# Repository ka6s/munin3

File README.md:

# munin3
This is a KICAD version of the Munin 3 100W amplifer designed by Kjell - LA2NI. Note that some of the DNI parts have been left out of the schematic. 

The design has been updated to the point that it reliably can balance the two transistors. Haven't verified the
Test Point for that operation yet.

Kjell, LA2NI has reviewed the design and found an error on my part when I did flooding of the power 
transformer.  Kicad didn't really do what I expected. I had to beef up these connections by hand. He also
found a couple errors in my schematic, and I found another later.. these issues have all been 
fixed.

The amplifier seems to work! 

Use the files in gerbers/munin3_v1.1.zip

Steve KA6S

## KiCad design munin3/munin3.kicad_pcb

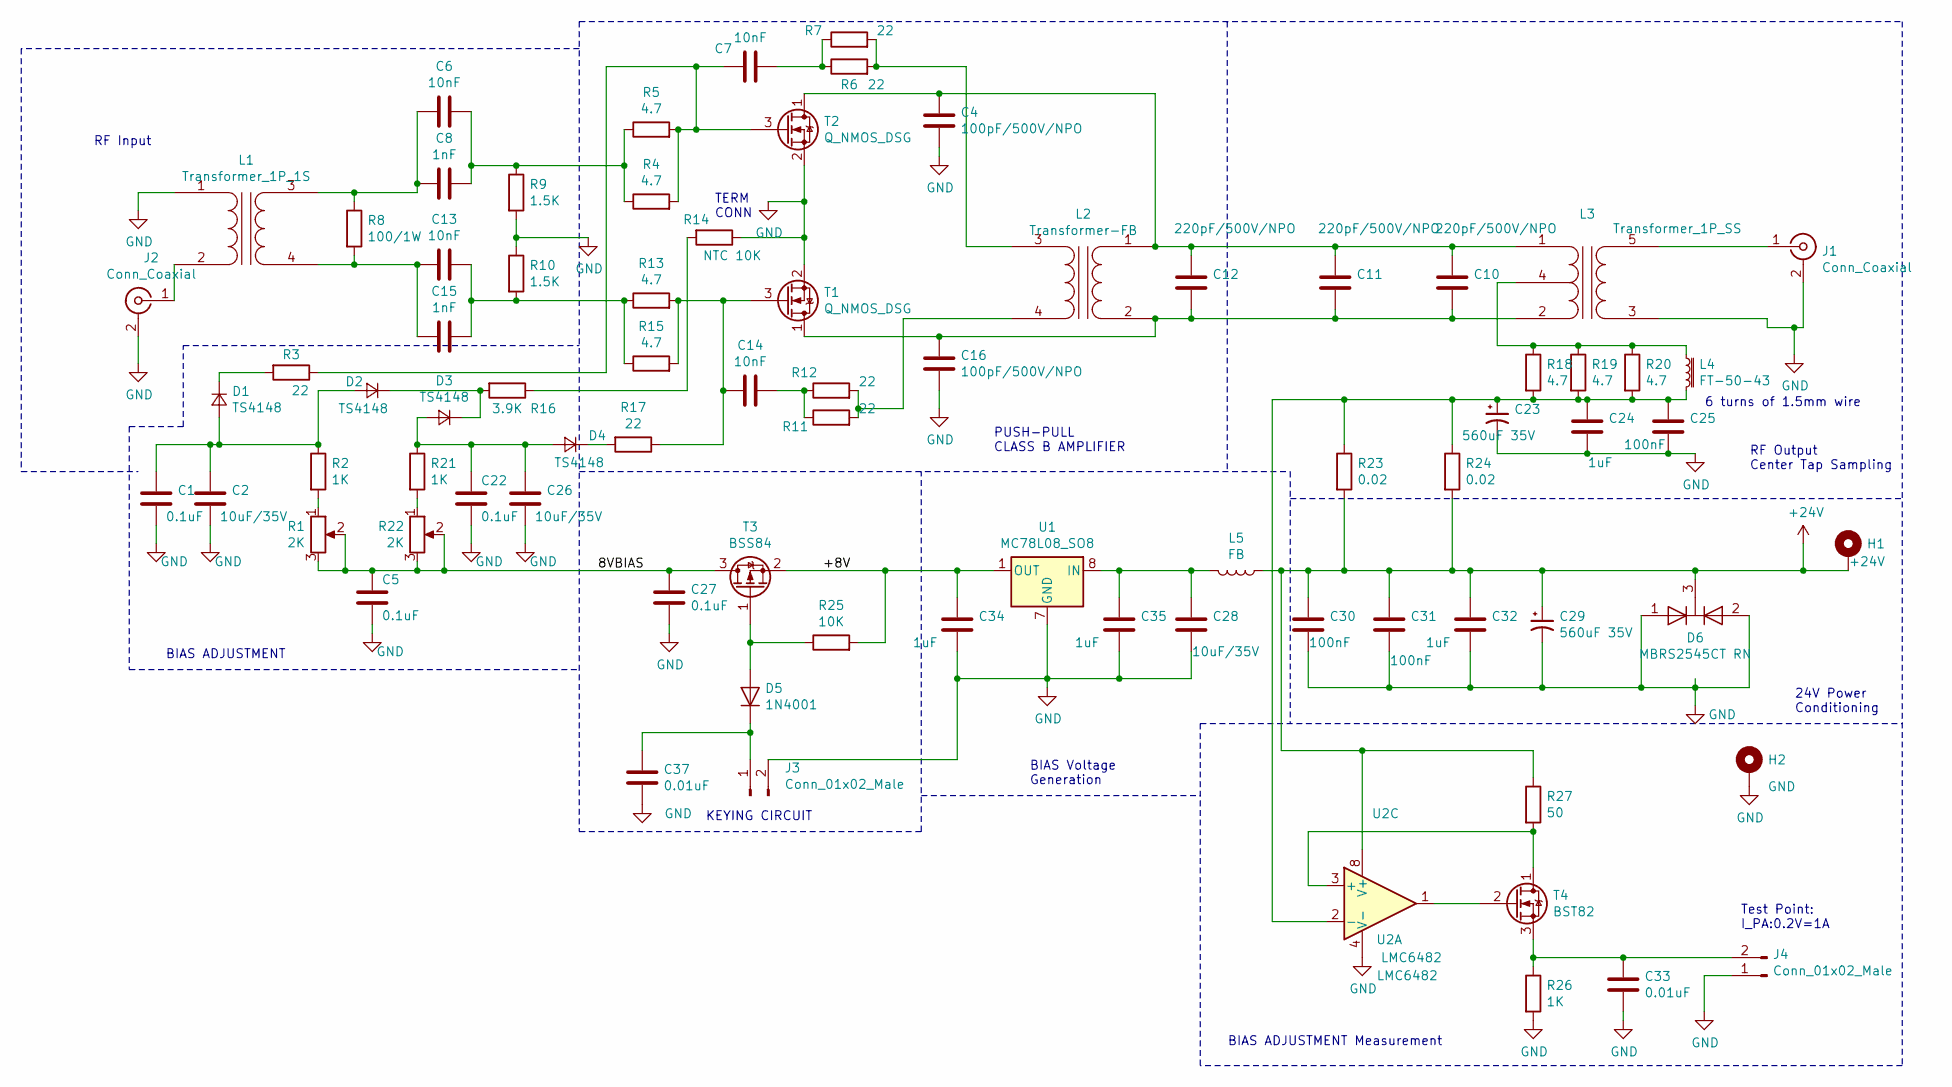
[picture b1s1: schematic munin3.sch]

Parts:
C1, C5, C22: 0.1uF; C_0805_2012Metric_Pad1.15x1.40mm_HandSolder; Mouser Part Number 0805DD104KAT2A
C2, C26, C28: 10uF/35V; C_1206_3216Metric_Pad1.42x1.75mm_HandSolder; Mouser Part Number GMK316AB7106KL-TR
C4: 100pF/500V/NPO; C_0805_2012Metric_Pad1.15x1.40mm_HandSolder; Mouser Part Number 603-CC206JRNPOBBN101
C6, C7, C13, C14: 10nF; C_0805_2012Metric_Pad1.15x1.40mm_HandSolder
C8, C15: 1nF; C_0805_2012Metric_Pad1.15x1.40mm_HandSolder
C10, C11, C12: 220pF/500V/NPO; C_1206_3216Metric_Pad1.42x1.75mm_HandSolder; Mouser Part Number 81-GRM31A5C2H221JW1D
C16: 100pF/500V/NPO; C_1206_3216Metric_Pad1.42x1.75mm_HandSolder; Mouser Part Number 603-CC206JRNPOBBN101
C23, C29: 560uF 35V; CP_Elec_10x10; Mouser Part Number 661-EMZS350ARA561MJA
C24, C32: 1uF; C_0805_2012Metric_Pad1.15x1.40mm_HandSolder; Mouser Part Number 667-EEE-FT1V561AP
C25, C30, C31: 100nF; C_0805_2012Metric_Pad1.15x1.40mm_HandSolder; Mouser Part Number 80-C0805C104J5RAUTO
C27: 0.1uF; C_0805_2012Metric_Pad1.15x1.40mm_HandSolder
C33, C37: 0.01uF; C_0805_2012Metric_Pad1.15x1.40mm_HandSolder; Mouser Part Number 80-C0805C103K5TAUTO
C34, C35: 1uF; C_0805_2012Metric_Pad1.15x1.40mm_HandSolder; Mouser Part Number 80-C0805C104J5RAUTO
D1, D2, D3, D4: TS4148; D_0805_2012Metric_Pad1.15x1.40mm_HandSolder; Mouser Part Number 821-TS4148RYG
D5: 1N4001; D_0805_2012Metric_Pad1.15x1.40mm_HandSolder
D6: MBRS2545CT RN; TO-263-3_TabPin4; Mouser Part Number 821-MBRS2545CTRN
H1: +24V; MountingHole_11mm_M4_square_Via
H2: GND; MountingHole_11mm_M4_square_Via
J1, J2: Conn_Coaxial; SMA_Amphenol_132291_Vertical
J3, J4: Conn_01x02_Male; PinHeader_1x02_P2.54mm_Vertical
L1: Transformer_1P_1S; RF_Input_XFMR
L2: Transformer-FB; RF_FB_XFMR
L3: Transformer_1P_SS; HF_Power_Xfmr
L4: FT-50-43; RF_Choke
L5: FB; L_MUNIN_FB; Mouser Part Number 704-MFBM1V2012-101-R
R1, R22: 2K; Potentiometer_Bourns_3386P_Vertical; Mouser Part Number 81-PV12P202A01B00
R2, R21, R26: 1K; R_0805_2012Metric_Pad1.15x1.40mm_HandSolder
R3, R17: 22; R_0805_2012Metric_Pad1.15x1.40mm_HandSolder
R4, R5, R13, R15, R18, R19, R20: 4.7; R_0805_2012Metric_Pad1.15x1.40mm_HandSolder
R6, R7, R11, R12: 22; R_0805_2012Metric_Pad1.15x1.40mm_HandSolder; Mouser Part Number 660-SG73P2ATTD220G
R8: 100/1W; R_1812_4532Metric_Pad1.30x3.40mm_HandSolder; Mouser Part Number 667-ERJ-12NF1000U
R9, R10: 1.5K; R_0805_2012Metric_Pad1.15x1.40mm_HandSolder
R14: NTC 10K; R_Axial_DIN0204_L3.6mm_D1.6mm_P2.54mm_Vertical
R16: 3.9K; R_0805_2012Metric_Pad1.15x1.40mm_HandSolder
R23, R24: 0.02; R_2512_6332Metric_Pad1.52x3.35mm_HandSolder; Mouser Part Number 652-CRA2512FZ-R20ELF
R25: 10K; R_0805_2012Metric_Pad1.15x1.40mm_HandSolder
R27: 50; R_0805_2012Metric_Pad1.15x1.40mm_HandSolder
T1, T2: Q_NMOS_DSG; RD100HHF1
T3: BSS84; SOT-23; Mouser Part Number 771-BSS84AKVL
T4: BST82; SOT-23; Mouser Part Number 771-BST82235
U1: MC78L08_SO8; SOIC-8_3.9x4.9mm_P1.27mm; Mouser Part Number 511-L78L08ACD-TR
U2: LMC6482; SOIC-8_3.9x4.9mm_P1.27mm; Mouser Part Number 511-LMC6482IST

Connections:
+24V: C29.1, C30.1, C31.1, C32.1, D6.3 (K), H1.1, L5.1, R23.2, R24.2, R27.1, U2.8 (V+)
/8VBIAS: C5.1, C27.1, R1.2, R1.3, R22.2, R22.3, T3.3 (D)
/+8V: C34.1, R25.2, T3.2 (S), U1.1 (OUT)
GND: C1.2, C2.2, C4.2, C5.2, C16.2, C22.2, C23.2, C24.2, C25.2, C26.2, C27.2, C28.2, C29.2, C30.2, C31.2, C32.2, C33.2, C34.2, C35.2, C37.2, D6.1 (A), D6.2 (A), H2.1, J1.2 (Ext), J2.2 (Ext), J3.2, J4.1, L1.1 (AA), L3.3 (AB), R9.2, R10.1, R14.1, R26.2, T1.2 (S), T2.2 (S), U1.2 (GND), U1.3 (GND), U1.6 (GND), U1.7 (GND), U2.4 (V-)
unnamed: C1.1, C2.1, D1.2 (A), D2.2 (A), R2.1
unnamed: C6.1, C8.1, R4.1, R5.1, R9.1
unnamed: C6.2, C8.2, L1.3 (SB), R8.1
unnamed: C7.1, R6.1, R7.1
unnamed: C7.2, R3.1, R4.2, R5.2, T2.3 (G)
unnamed: C4.1, C10.1, C11.1, C12.1, L2.1 (AA), L3.1 (SB), T2.1 (D)
unnamed: C10.2, C11.2, C12.2, C16.1, L2.2 (AB), L3.2 (SA), T1.1 (D)
unnamed: C13.1, C15.1, R10.2, R13.1, R15.1
unnamed: C13.2, C15.2, L1.4 (SA), R8.2
unnamed: C14.1, R11.1, R12.1
unnamed: C14.2, R13.2, R15.2, R17.1, T1.3 (G)
unnamed: C22.1, C26.1, D3.2 (A), D4.2 (A), R21.1
unnamed: C23.1, C24.1, C25.1, L4.2, R18.2, R19.2, R20.2, R23.1, R24.1, U2.2 (-)
unnamed: C28.1, C35.1, L5.2, U1.8 (IN)
unnamed: C33.1, J4.2, R26.1, T4.3 (S)
unnamed: C37.1, D5.1 (K), J3.1
unnamed: D1.1 (K), R3.2
unnamed: D2.1 (K), D3.1 (K), R16.2
unnamed: D4.1 (K), R17.2
unnamed: D5.2 (A), R25.1, T3.1 (G)
unnamed: J1.1 (In), L3.5 (AA)
unnamed: J2.1 (In), L1.2 (AB)
unnamed: L2.3 (SB), R6.2, R7.2
unnamed: L2.4 (SA), R11.2, R12.2
unnamed: L3.4 (SC), L4.1, R18.1, R19.1, R20.1
unnamed: R1.1, R2.2
unnamed: R14.2, R16.1
unnamed: R21.2, R22.1
unnamed: R27.2, T4.1 (D), U2.3 (+)
unnamed: T4.2 (G), U2.1

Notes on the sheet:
6 turns of 1.5mm wire
KEYING CIRCUIT
PUSH-PULL CLASS B AMPLIFIER
BIAS ADJUSTMENT
TERM CONN
Test Point: I_PA:0.2V=1A
BIAS ADJUSTMENT Measurement
24V Power Conditioning
BIAS Voltage Generation
RF Output Center Tap Sampling
RF Input

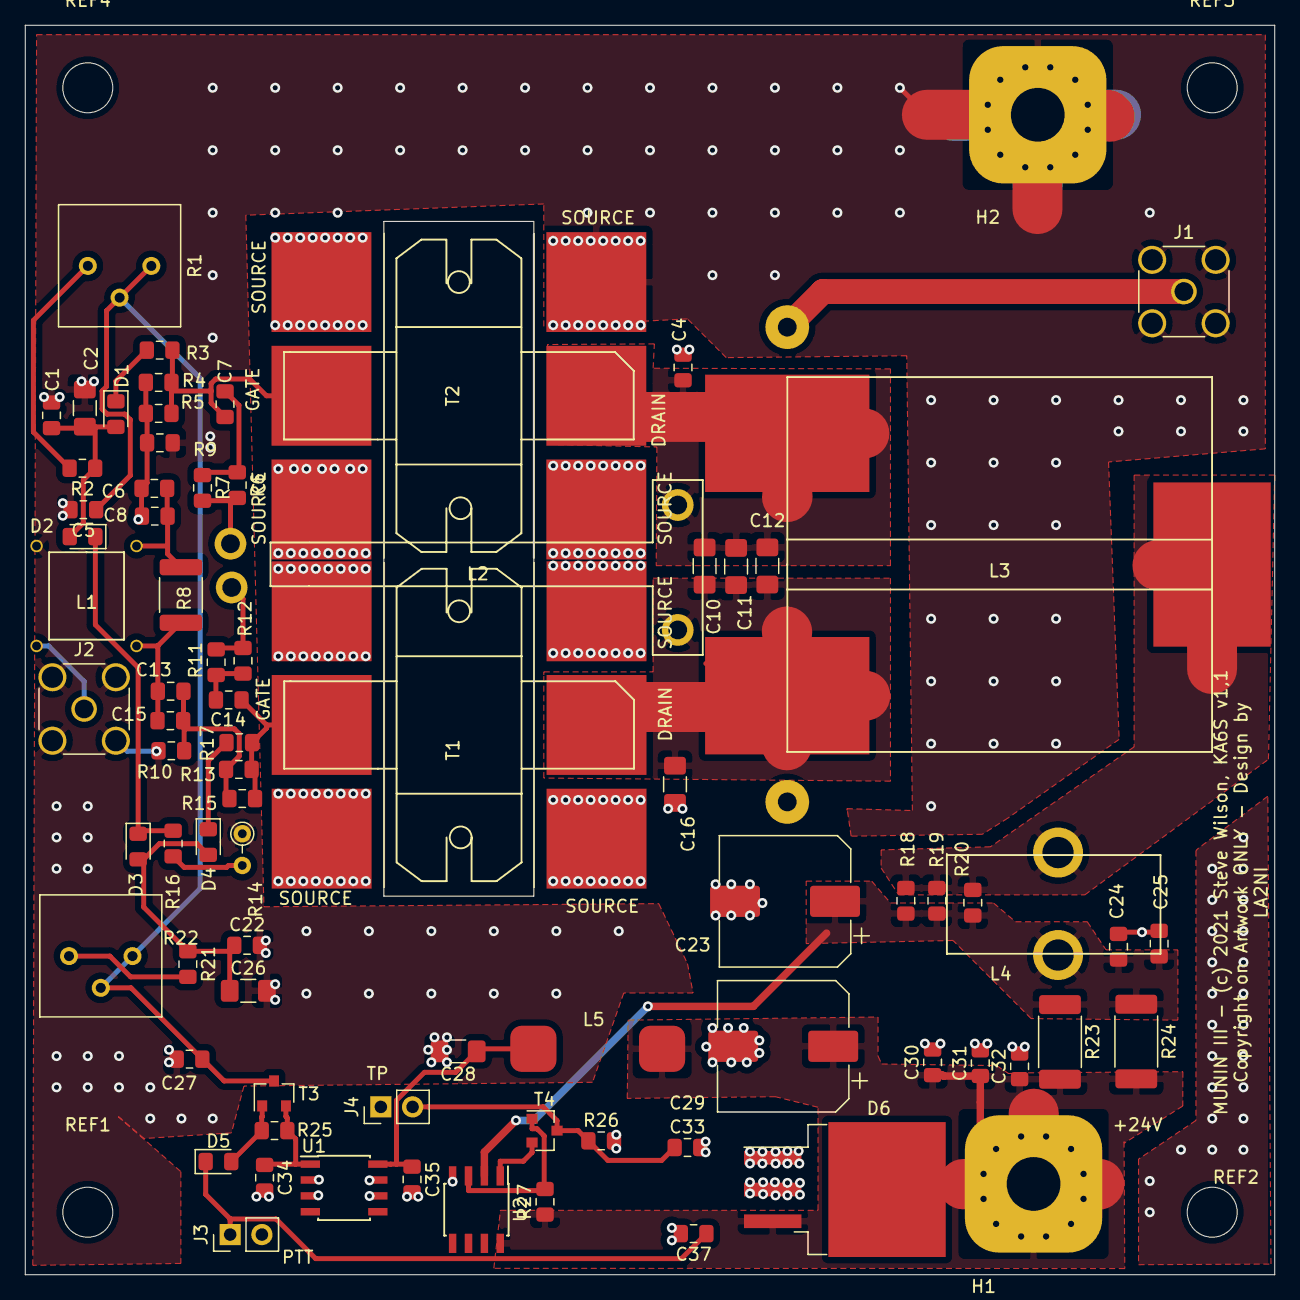
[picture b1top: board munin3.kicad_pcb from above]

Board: 2 copper layers, 100.0 x 100.0 mm, 83 parts (0 on the bottom side), 34 nets.

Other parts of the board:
REF1, REF2, REF3, REF4: MountingHole_6mm

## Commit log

2021-11-20 update status
2021-12-04 Fixed drain connection, fixed final xfmr connection
2021-12-05 Removed short between C8 and C15 on schem. Beefed up power/ground/Power Xfmr connections.
2021-12-05 Remove
2021-12-05 Status Updaet
2021-12-05 Update README.md with it works!
2021-12-05 Updated Version Number
2021-12-05 New Gerbers with fixes
2021-12-05 Remove older gerber zip
2021-12-05 Add v1_0 here

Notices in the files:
munin3/munin3.kicad_pcb:
MUNIN III - (c) 2021 Steve Wilson, KA6S v1,1
